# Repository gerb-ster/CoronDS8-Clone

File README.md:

# CoronDS8 Clone

This is a clone of the famous Coron DS8 DrumSytnh unit from the seventies. I've adapted it 
to a Eurorack module and included a small mod, a on-off-on 'weird' toggle switch, which 
generates even spacier drum sounds.

## Status: (Almost) Finished

- done: first schematic & board design
- done: breadboard and test
- done: design frontpanel
- done: order PCB and build prototype
- done: fully test the prototype
- todo: buid a proper faceplate

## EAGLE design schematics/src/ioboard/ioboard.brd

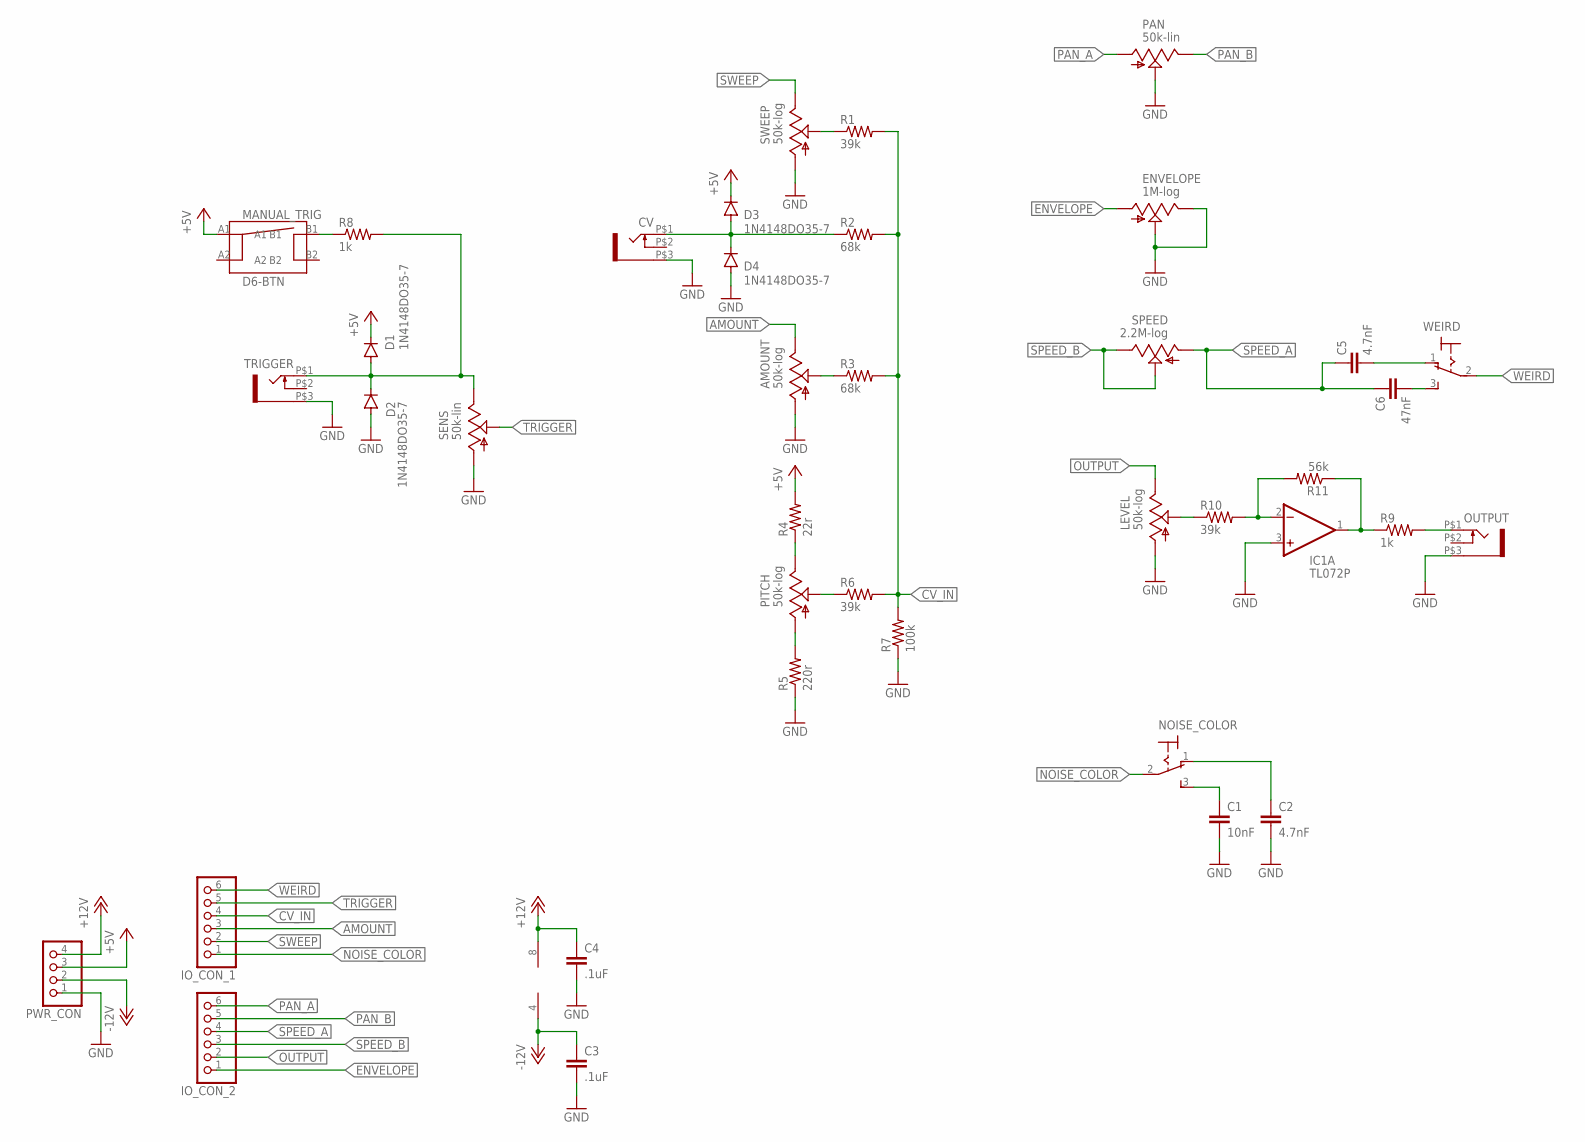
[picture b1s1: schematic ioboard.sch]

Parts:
AMOUNT: 50k-log; EVUF
C1: 10nF; C050-024X044
C2, C5: 4.7nF; C050-024X044
C3, C4: .1uF; C050-024X044
C6: 47nF; C050-024X044
CV: WQP-PJ301M-12_JACK
D1, D2, D3, D4: 1N4148DO35-7; DO35-7
ENVELOPE: 1M-log; EVUF
IC1: TL072P; DIL08
IO_CON_1, IO_CON_2: PINHD-1X6; 1X06
LEVEL: 50k-log; EVUF
MANUAL_TRIG: D6-BTN
NOISE_COLOR: M9040P
OUTPUT: WQP-PJ301M-12_JACK
PAN: 50k-lin; EVUF
PITCH: 50k-log; EVUF
PWR_CON: PINHD-1X4; 1X04
R1, R6, R10: 39k; 0207/7
R2, R3: 68k; 0207/7
R4: 22r; 0207/7
R5: 220r; 0207/7
R7: 100k; 0207/7
R8, R9: 1k; 0207/7
R11: 56k; 0207/7
SENS: 50k-lin; EVUF
SPEED: 2.2M-log; EVUF
SWEEP: 50k-log; EVUF
TRIGGER: WQP-PJ301M-12_JACK
WEIRD: M9040P

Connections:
+5V: D1.C, D3.C, MANUAL_TRIG.A1, PWR_CON.3, R4.2
+12V: C4.1, IC1.8 (V+), PWR_CON.4
-12V: C3.1, IC1.4 (V-), PWR_CON.2
AMOUNT: AMOUNT.3 (E), IO_CON_1.3
CV_IN: IO_CON_1.4, R1.2, R2.2, R3.2, R6.2, R7.2
ENVELOPE: ENVELOPE.1 (A), IO_CON_2.1
GND: AMOUNT.1 (A), C1.2, C2.2, C3.2, C4.2, CV.P$3 (1), D2.A, D4.A, ENVELOPE.2 (S), ENVELOPE.3 (E), IC1.3 (+IN), LEVEL.1 (A), OUTPUT.P$3 (1), PAN.2 (S), PWR_CON.1, R5.1, R7.1, SENS.1 (A), SWEEP.1 (A), TRIGGER.P$3 (1)
unnamed: PITCH.1 (A), R5.2
unnamed: PITCH.2 (S), R6.1
unnamed: PITCH.3 (E), R4.1
unnamed: AMOUNT.2 (S), R3.1
unnamed: CV.P$1 (2), D3.A, D4.C, R2.1
unnamed: R1.1, SWEEP.2 (S)
unnamed: C1.1, NOISE_COLOR.3 (S)
unnamed: IC1.2 (-IN), R10.2, R11.2
unnamed: C2.1, NOISE_COLOR.1 (O)
unnamed: MANUAL_TRIG.B1, R8.1
unnamed: C6.2, WEIRD.3 (S)
unnamed: OUTPUT.P$1 (2), R9.2
unnamed: IC1.1 (OUT), R9.1, R11.1
unnamed: LEVEL.2 (S), R10.1
unnamed: C5.2, WEIRD.1 (O)
unnamed: D1.A, D2.C, R8.2, SENS.3 (E), TRIGGER.P$1 (2)
NOISE_COLOR: IO_CON_1.1, NOISE_COLOR.2
OUTPUT: IO_CON_2.2, LEVEL.3 (E)
PAN_A: IO_CON_2.6, PAN.1 (A)
PAN_B: IO_CON_2.5, PAN.3 (E)
SPEED_A: C5.1, C6.1, IO_CON_2.4, SPEED.1 (A)
SPEED_B: IO_CON_2.3, SPEED.2 (S), SPEED.3 (E)
SWEEP: IO_CON_1.2, SWEEP.3 (E)
TRIGGER: IO_CON_1.5, SENS.2 (S)
WEIRD: IO_CON_1.6, WEIRD.2

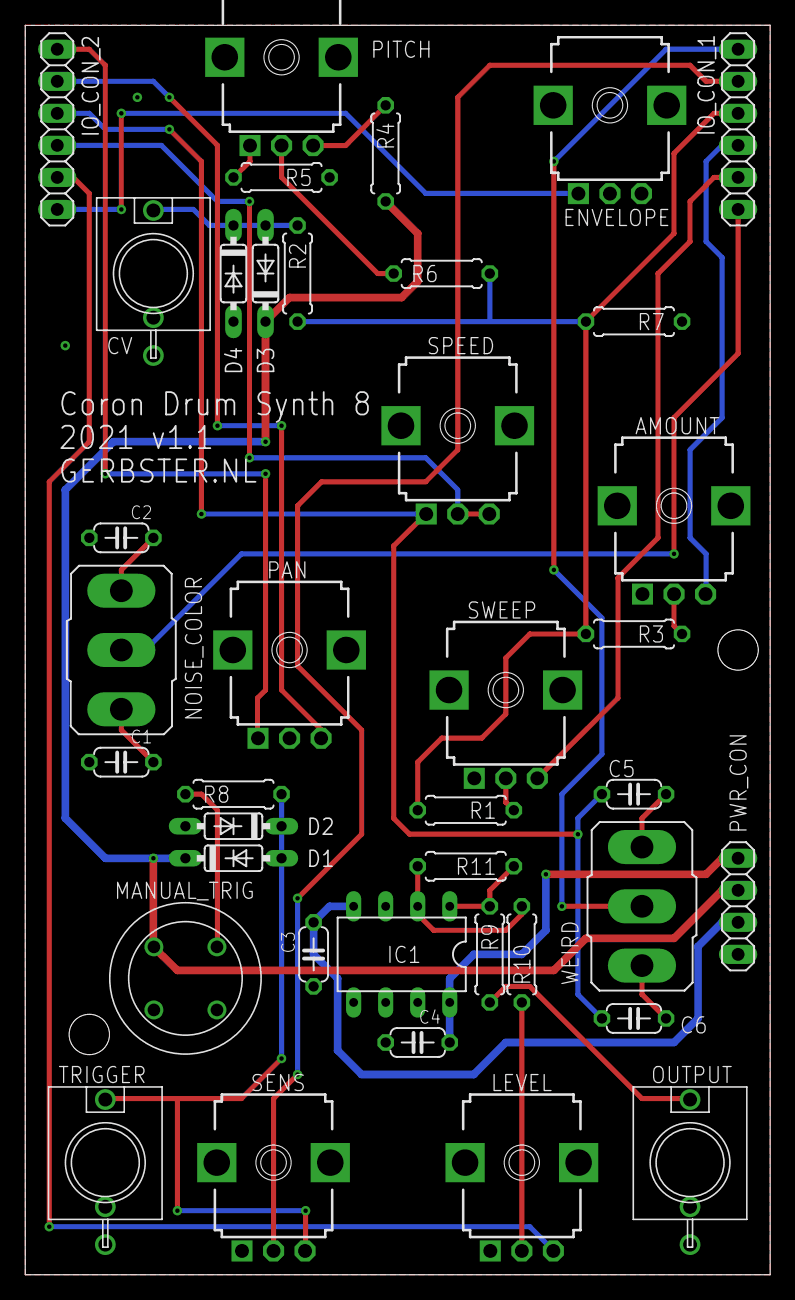
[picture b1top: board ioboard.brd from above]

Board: 2 copper layers, 59.1 x 99.1 mm, 39 parts (0 on the bottom side), 32 nets.

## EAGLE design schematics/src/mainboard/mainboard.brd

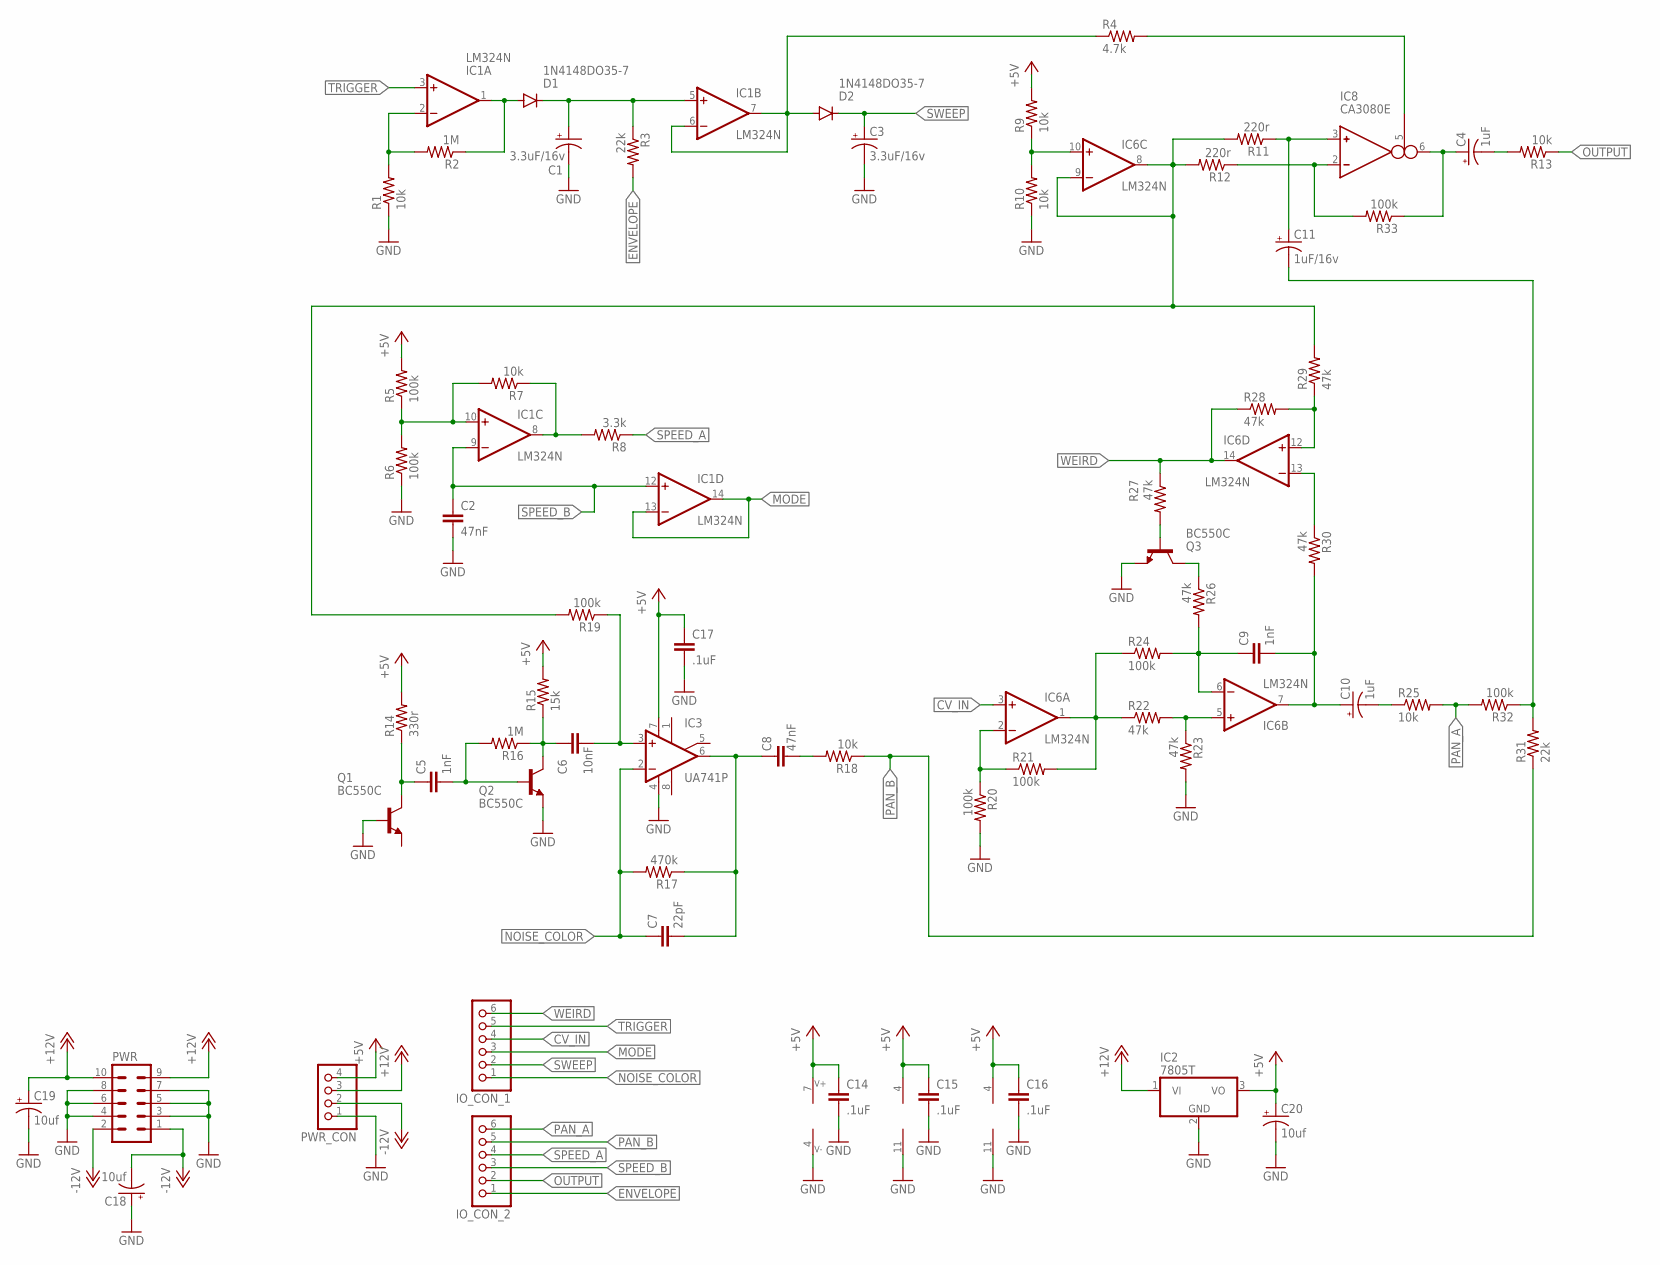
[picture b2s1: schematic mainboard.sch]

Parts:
C1, C3: 3.3uF/16v; E2,5-6
C2, C8: 47nF; C050-024X044
C4, C10: 1uF; E2,5-6
C5, C9: 1nF; C050-024X044
C6: 10nF; C050-024X044
C7: 22pF; C050-024X044
C11: 1uF/16v; E2,5-6
C14, C15, C16, C17: .1uF; C050-024X044
C18, C19, C20: 10uf; E2,5-5
D1, D2: 1N4148DO35-7; DO35-7
IC1, IC6: LM324N; DIL14
IC2: 7805T; TO220H
IC3: UA741P; DIL08
IC8: CA3080E; DIL08
IO_CON_1, IO_CON_2: PINHD-1X6; 1X06
PWR: ML10
PWR_CON: PINHD-1X4; 1X04
Q1, Q2, Q3: BC550C; TO92-EBC
R1, R7, R9, R10, R13, R18, R25: 10k; 0207/7
R2, R16: 1M; 0207/7
R3, R31: 22k; 0207/7
R4: 4.7k; 0207/7
R5, R6, R19, R20, R21, R24, R32, R33: 100k; 0207/7
R8: 3.3k; 0207/7
R11, R12: 220r; 0207/7
R14: 330r; 0207/7
R15: 15k; 0207/7
R17: 470k; 0207/7
R22, R23, R26, R27, R28, R29, R30: 47k; 0207/7

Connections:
+5V: C14.1, C15.1, C16.1, C17.1, C20.+, IC1.4 (V+), IC2.3 (VO), IC3.7 (V+), IC6.4 (V+), IC8.7 (V+), PWR_CON.4, R5.2, R9.2, R14.2, R15.2
+12V: C19.+, IC2.1 (VI), PWR.9, PWR.10, PWR_CON.3
-12V: C18.-, PWR.1, PWR.2, PWR_CON.2
CV_IN: IC6.3 (+IN), IO_CON_1.4
ENVELOPE: IO_CON_2.1, R3.2
GND: C1.-, C2.2, C3.-, C14.2, C15.2, C16.2, C17.2, C18.+, C19.-, C20.-, IC1.11 (V-), IC2.2 (GND), IC3.4 (V-), IC6.11 (V-), IC8.4 (V-), PWR.3, PWR.4, PWR.5, PWR.6, PWR.7, PWR.8, PWR_CON.1, Q1.B, Q2.E, Q3.E, R1.1, R6.1, R10.1, R20.2, R23.2
MODE: IC1.13 (-IN), IC1.14 (OUT), IO_CON_1.3
unnamed: IC1.2 (-IN), R1.2, R2.2
unnamed: D1.A, IC1.1 (OUT), R2.1
unnamed: C1.+, D1.C, IC1.5 (+IN), R3.1
unnamed: IC1.10 (+IN), R5.1, R6.2, R7.2
unnamed: D2.A, IC1.6 (-IN), IC1.7 (OUT), R4.1
unnamed: IC8.5 (I_BIAS), R4.2
unnamed: IC1.8 (OUT), R7.1, R8.2
unnamed: IC6.10 (+IN), R9.1, R10.2
unnamed: IC6.8 (OUT), IC6.9 (-IN), R11.2, R12.2, R19.2, R29.2
unnamed: C11.+, IC8.3 (IN_P), R11.1
unnamed: C4.+, IC8.6 (OUT), R33.1
unnamed: C5.1, Q1.C, R14.1
unnamed: C5.2, Q2.B, R16.2
unnamed: C4.-, R13.2
unnamed: C6.1, Q2.C, R15.1, R16.1
unnamed: C6.2, IC3.3 (+IN), R19.1
unnamed: C8.2, R18.2
unnamed: C7.2, C8.1, IC3.6 (OUT), R17.1
unnamed: IC6.5 (+IN), R22.2, R23.1
unnamed: IC6.2 (-IN), R20.1, R21.1
unnamed: IC6.1 (OUT), R21.2, R22.1, R24.1
unnamed: C9.1, IC6.6 (-IN), R24.2, R26.2
unnamed: C9.2, C10.+, IC6.7 (OUT), R30.2
unnamed: C10.-, R25.1
unnamed: Q3.C, R26.1
unnamed: Q3.B, R27.2
unnamed: IC8.2 (IN_N), R12.1, R33.2
unnamed: IC6.13 (-IN), R30.1
unnamed: C11.-, R31.2, R32.1
unnamed: IC6.12 (+IN), R28.2, R29.1
NOISE_COLOR: C7.1, IC3.2 (-IN), IO_CON_1.1, R17.2
OUTPUT: IO_CON_2.2, R13.1
PAN_A: IO_CON_2.6, R25.2, R32.2
PAN_B: IO_CON_2.5, R18.1, R31.1
SPEED_A: IO_CON_2.4, R8.1
SPEED_B: C2.1, IC1.9 (-IN), IC1.12 (+IN), IO_CON_2.3
SWEEP: C3.+, D2.C, IO_CON_1.2
TRIGGER: IC1.3 (+IN), IO_CON_1.5
WEIRD: IC6.14 (OUT), IO_CON_1.6, R27.1, R28.1

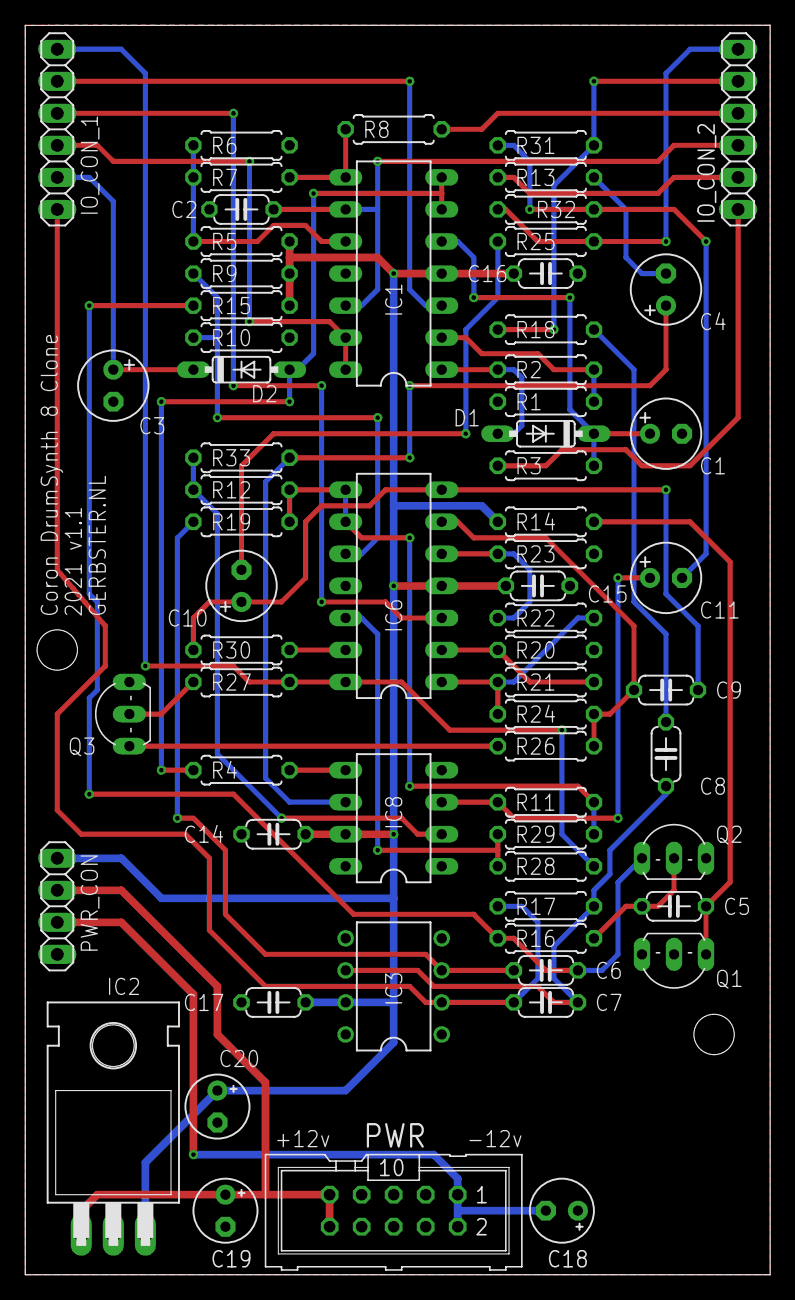
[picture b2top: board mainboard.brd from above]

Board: 2 copper layers, 59.1 x 99.1 mm, 65 parts (0 on the bottom side), 46 nets.

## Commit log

2021-05-07 Added files and structure
2021-05-10 Added Status
2021-05-11 Added Status & Images
2021-06-15 Updated Schematics, Fixed Power Socket orientation
2021-07-19 Fixed minor issues, added documentation and updated some faceplates
2021-08-06 Updated some schematics and docs
2021-08-10 Fixed some bugs and updated documentation
2022-04-20 Minor updates
2022-04-20 Some updates & bugfixes
2022-04-22 Fixed schematics & descriptions
2022-05-17 Updated Firmware
2022-05-18 Updated Faceplates
2022-05-18 Fixed issues
2022-05-21 Fixed schematics
2022-05-25 General updates
2022-06-13 Faceplates & Bugfixes
